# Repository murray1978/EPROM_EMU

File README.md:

# EPROM_EMU
EPROM Emulator for [Sergey's](http://www.malinov.com/Home/sergeys-projects/minimax8085) 8085 board.
Second revison is in progress, 12/5/21, check the readme in version two for errors on the board.

## Programming
The monitor rom can be used to upload the emulator code for the board.
Install the battery backup on to the 8085 borad then you will not need to upload each time you need to use the board.

## Source
As is where is, one carfull lady owner.
Some functions are copied from the monitor code, but it does relie on the monitor rom to setup the 8251 UART before use.
Code is just an outline now with a few ideas in comments.

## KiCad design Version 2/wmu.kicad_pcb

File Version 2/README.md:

# EPROM_EMU
EPROM Emulator for [Sergey's](http://www.malinov.com/Home/sergeys-projects/minimax8085) 8085 board, This is the Second revision.

## Mistakes
1. IC1 (74LS137), Pins 9 and 7, will never get triggered, the correct connections are pins 15 and 14.
   Fix with a solder a jumper bridge between 9 to 15 and 7 to 14. Schmatic is correct

## Substitutions 
1. U1 can be replaced with a 74LS138
2. the RAM, U10 as6c62256, can be replaced with cy62256? need to confirm pinout.

## Programming
The monitor rom can be used to upload the emulator code for the board.
Install the battery backup on to the 8085 borad then you will not need to upload each time you need to use the board.

## Source
As is where is, one carfull lady owner.
Some functions are copied from the monitor code, but it does relie on the monitor rom to setup the 8251 UART before use.
Code is just an outline now with a few ideas in comments.

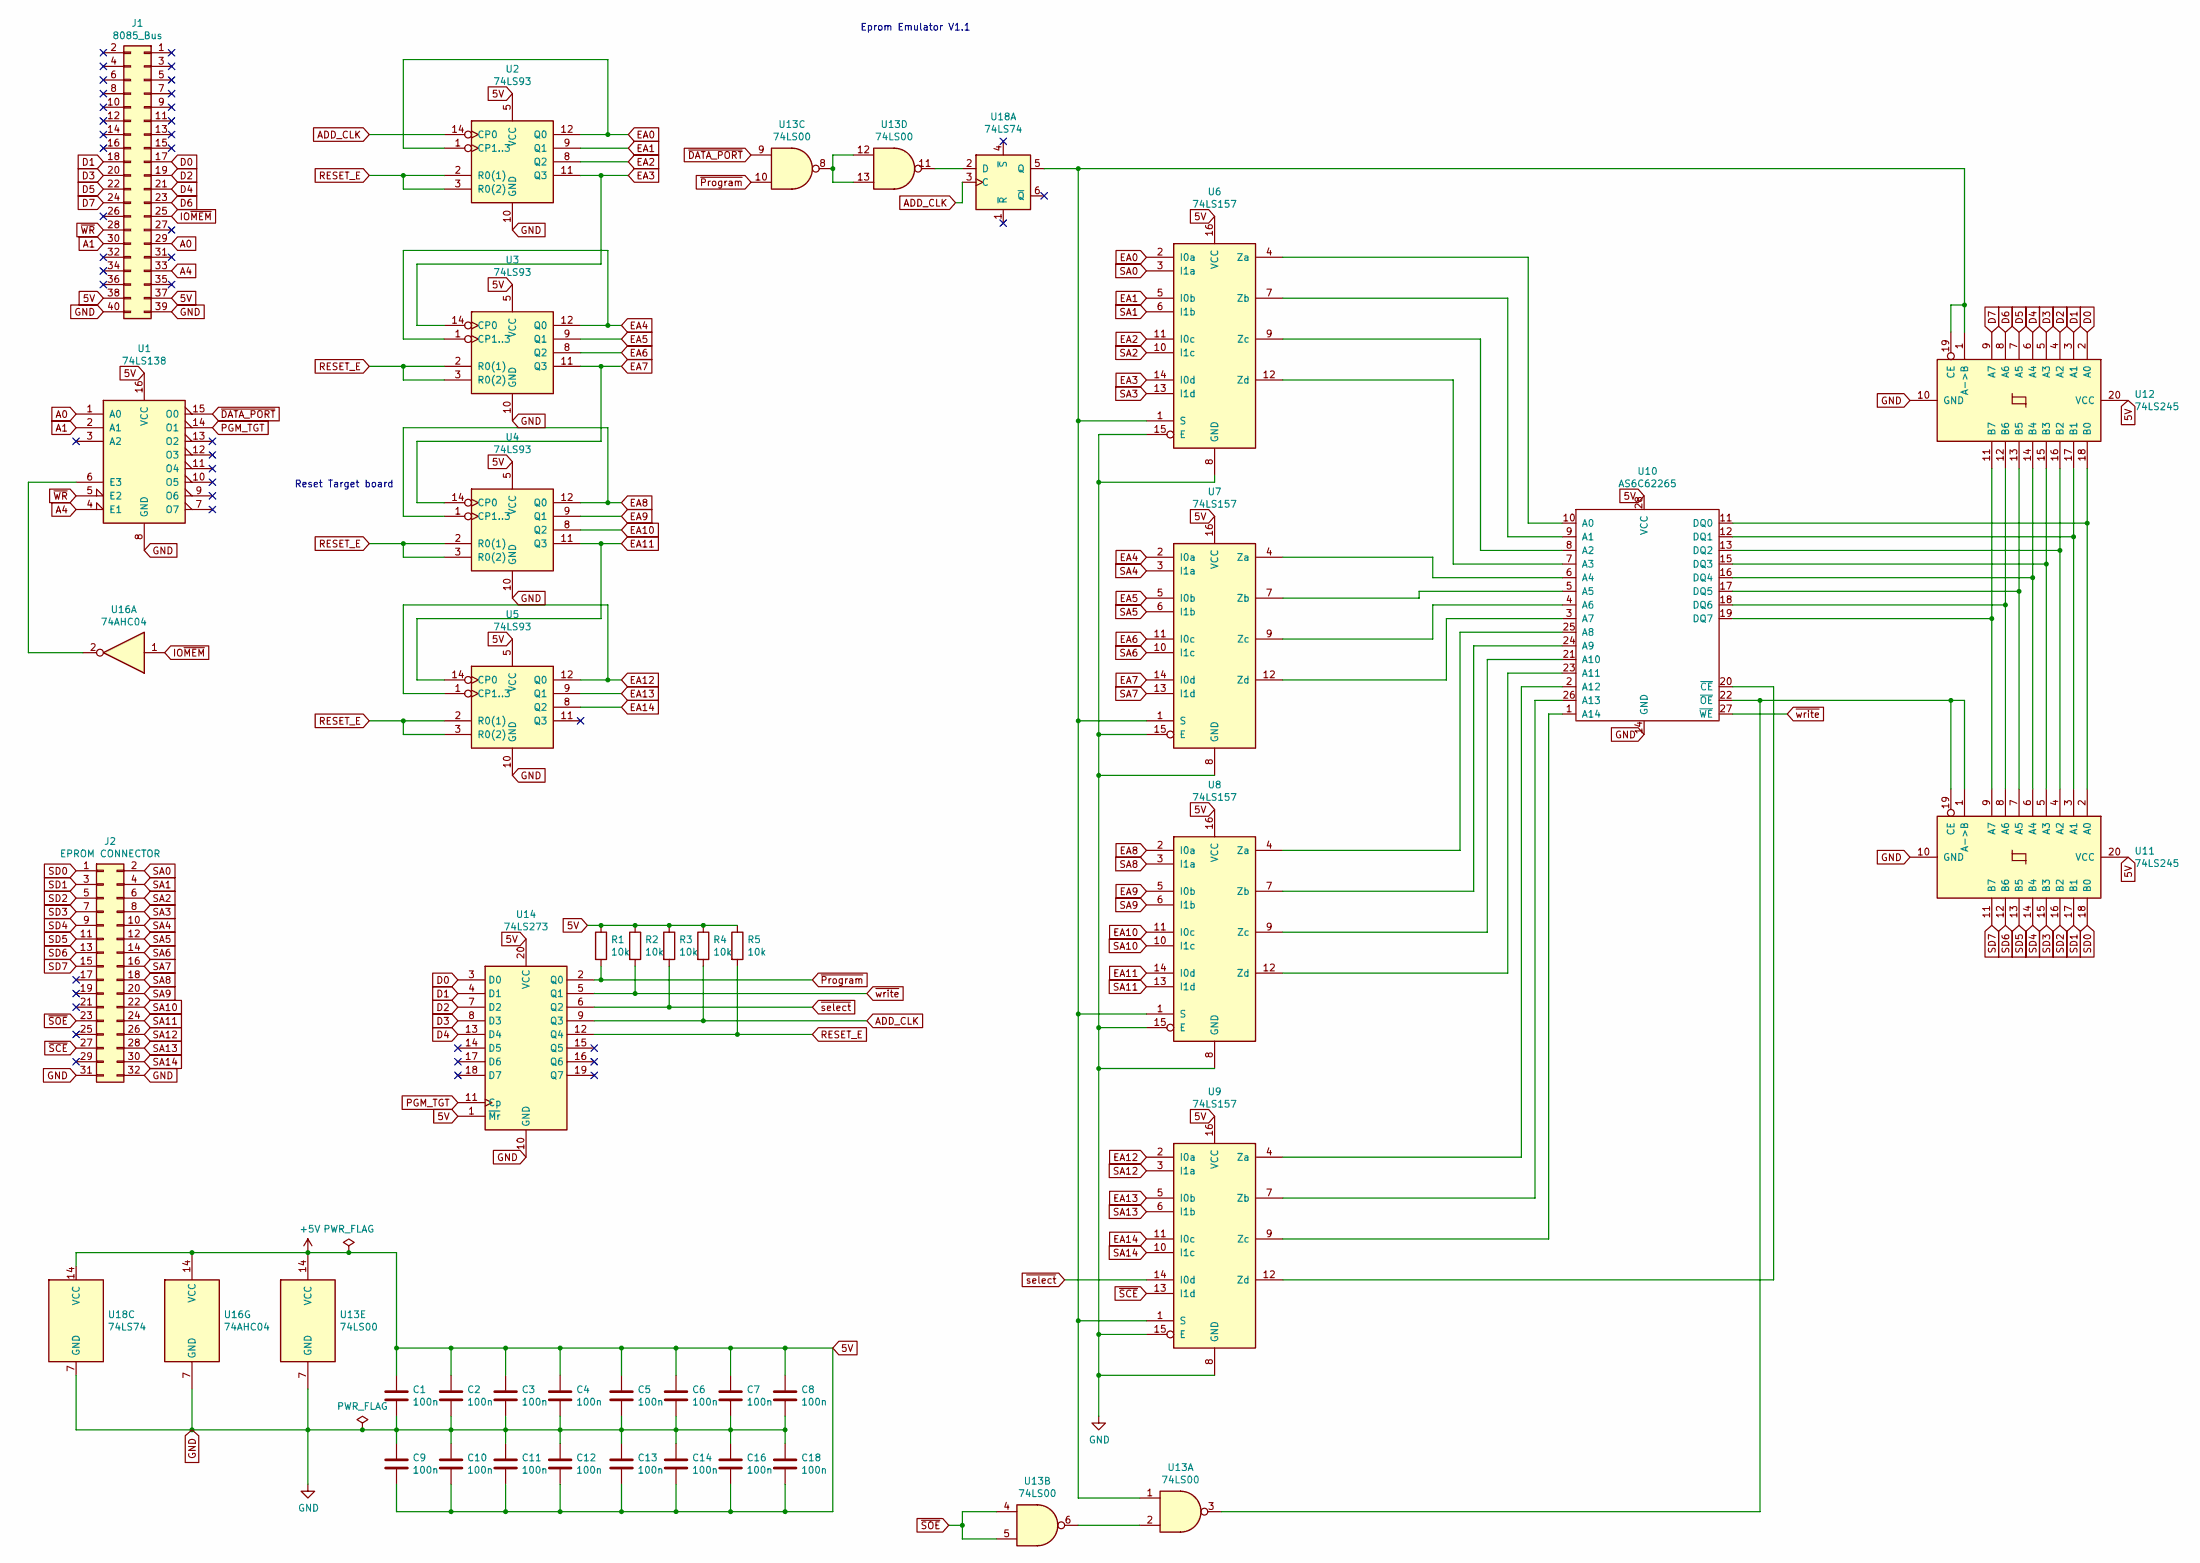
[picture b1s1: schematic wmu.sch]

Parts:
C1, C2, C3, C4, C5, C6, C7, C8, C9, C10, C11, C12, C13, C14, C16, C18: 100n; C_Rect_L7.0mm_W2.5mm_P5.00mm
J1: 8085_Bus; PinSocket_2x20_P2.54mm_Vertical
J2: EPROM CONNECTOR; IDC-Header_2x17_P2.54mm_Vertical
R1, R2, R3, R4, R5: 10k; R_Axial_DIN0207_L6.3mm_D2.5mm_P10.16mm_Horizontal
U1: 74LS138; DIP-16_W7.62mm_LongPads
U2, U3, U4, U5: 74LS93; DIP-14_W7.62mm_Socket
U6, U7, U8, U9: 74LS157; DIP-16_W7.62mm_Socket
U10: AS6C62265; DIP-28_W15.24mm_Socket
U11, U12: 74LS245; DIP-20_W7.62mm_Socket
U13: 74LS00; DIP-14_W7.62mm_Socket
U14: 74LS273; DIP-20_W7.62mm_Socket
U16: 74AHC04; DIP-14_W7.62mm_Socket
U18: 74LS74; DIP-14_W7.62mm_LongPads

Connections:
5V: C1.1, C2.1, C3.1, C4.1, C5.1, C6.1, C7.1, C8.1, C9.2, C10.2, C11.2, C12.2, C13.2, C14.2, C16.2, C18.2, J1.37, J1.38, R1.1, R2.1, R3.1, R4.1, R5.1, U1.16 (VCC), U2.5 (VCC), U3.5 (VCC), U4.5 (VCC), U5.5 (VCC), U6.16 (VCC), U7.16 (VCC), U8.16 (VCC), U9.16 (VCC), U10.28 (VCC), U11.20 (VCC), U12.20 (VCC), U13.14 (VCC), U14.1 (~Mr), U14.20 (VCC), U16.14 (VCC), U18.14 (VCC)
A0: J1.29, U1.1 (A0)
A1: J1.30, U1.2 (A1)
A4: J1.33, U1.4 (E1)
ADD_CLK: R4.2, U2.14 (CP0), U14.9 (Q3), U18.3 (C)
D0: J1.17, U12.2 (A0), U14.3 (D0)
D1: J1.18, U12.3 (A1), U14.4 (D1)
D2: J1.19, U12.4 (A2), U14.7 (D2)
D3: J1.20, U12.5 (A3), U14.8 (D3)
D4: J1.21, U12.6 (A4), U14.13 (D4)
D5: J1.22, U12.7 (A5)
D6: J1.23, U12.8 (A6)
D7: J1.24, U12.9 (A7)
EA0: U2.1 (CP1..3), U2.12 (Q0), U6.2 (I0a)
EA1: U2.9 (Q1), U6.5 (I0b)
EA2: U2.8 (Q2), U6.11 (I0c)
EA3: U2.11 (Q3), U3.14 (CP0), U6.14 (I0d)
EA4: U3.1 (CP1..3), U3.12 (Q0), U7.2 (I0a)
EA5: U3.9 (Q1), U7.5 (I0b)
EA6: U3.8 (Q2), U7.11 (I0c)
EA7: U3.11 (Q3), U4.14 (CP0), U7.14 (I0d)
EA8: U4.1 (CP1..3), U4.12 (Q0), U8.2 (I0a)
EA9: U4.9 (Q1), U8.5 (I0b)
EA10: U4.8 (Q2), U8.11 (I0c)
EA11: U4.11 (Q3), U5.14 (CP0), U8.14 (I0d)
EA12: U5.1 (CP1..3), U5.12 (Q0), U9.2 (I0a)
EA13: U5.9 (Q1), U9.5 (I0b)
EA14: U5.8 (Q2), U9.11 (I0c)
GND: C1.2, C2.2, C3.2, C4.2, C5.2, C6.2, C7.2, C8.2, C9.1, C10.1, C11.1, C12.1, C13.1, C14.1, C16.1, C18.1, J1.39, J1.40, J2.31, J2.32, U1.8 (GND), U2.10 (GND), U3.10 (GND), U4.10 (GND), U5.10 (GND), U6.8 (GND), U6.15 (E), U7.8 (GND), U7.15 (E), U8.8 (GND), U8.15 (E), U9.8 (GND), U9.15 (E), U10.14 (GND), U11.10 (GND), U12.10 (GND), U13.7 (GND), U14.10 (GND), U16.7 (GND), U18.7 (GND)
IO~MEM: J1.25, U16.1
unnamed: U1.6 (E3), U16.2
unnamed: U9.9 (Zc), U10.1 (A14)
unnamed: U9.4 (Za), U10.2 (A12)
unnamed: U7.12 (Zd), U10.3 (A7)
unnamed: U7.9 (Zc), U10.4 (A6)
unnamed: U7.7 (Zb), U10.5 (A5)
unnamed: U7.4 (Za), U10.6 (A4)
unnamed: U6.12 (Zd), U10.7 (A3)
unnamed: U6.9 (Zc), U10.8 (A2)
unnamed: U6.7 (Zb), U10.9 (A1)
unnamed: U6.4 (Za), U10.10 (A0)
unnamed: U10.11 (DQ0), U11.2 (A0), U12.18 (B0)
unnamed: U10.12 (DQ1), U11.3 (A1), U12.17 (B1)
unnamed: U10.13 (DQ2), U11.4 (A2), U12.16 (B2)
unnamed: U10.15 (DQ3), U11.5 (A3), U12.15 (B3)
unnamed: U10.16 (DQ4), U11.6 (A4), U12.14 (B4)
unnamed: U10.17 (DQ5), U11.7 (A5), U12.13 (B5)
unnamed: U10.18 (DQ6), U11.8 (A6), U12.12 (B6)
unnamed: U10.19 (DQ7), U11.9 (A7), U12.11 (B7)
unnamed: U9.12 (Zd), U10.20 (~CE)
unnamed: U8.9 (Zc), U10.21 (A10)
unnamed: U10.22 (~OE), U11.1 (A->B), U11.19 (CE), U13.3
unnamed: U8.12 (Zd), U10.23 (A11)
unnamed: U8.7 (Zb), U10.24 (A9)
unnamed: U8.4 (Za), U10.25 (A8)
unnamed: U9.7 (Zb), U10.26 (A13)
unnamed: U6.1 (S), U7.1 (S), U8.1 (S), U9.1 (S), U12.1 (A->B), U12.19 (CE), U13.1, U18.5 (Q)
unnamed: U13.2, U13.6
unnamed: U13.11, U18.2 (D)
unnamed: U13.8, U13.12, U13.13
PGM_TGT: U1.7 (O7), U1.14 (O1), U14.11 (Cp)
RESET_E: R5.2, U2.2 (R0(1)), U2.3 (R0(2)), U3.2 (R0(1)), U3.3 (R0(2)), U4.2 (R0(1)), U4.3 (R0(2)), U5.2 (R0(1)), U5.3 (R0(2)), U14.12 (Q4)
SA0: J2.2, U6.3 (I1a)
SA1: J2.4, U6.6 (I1b)
SA2: J2.6, U6.10 (I1c)
SA3: J2.8, U6.13 (I1d)
SA4: J2.10, U7.3 (I1a)
SA5: J2.12, U7.6 (I1b)
SA6: J2.14, U7.10 (I1c)
SA7: J2.16, U7.13 (I1d)
SA8: J2.18, U8.3 (I1a)
SA9: J2.20, U8.6 (I1b)
SA10: J2.22, U8.10 (I1c)
SA11: J2.24, U8.13 (I1d)
SA12: J2.26, U9.3 (I1a)
SA13: J2.28, U9.6 (I1b)
SA14: J2.30, U9.10 (I1c)
SD0: J2.1, U11.18 (B0)
SD1: J2.3, U11.17 (B1)
SD2: J2.5, U11.16 (B2)
SD3: J2.7, U11.15 (B3)
SD4: J2.9, U11.14 (B4)
SD5: J2.11, U11.13 (B5)
SD6: J2.13, U11.12 (B6)
SD7: J2.15, U11.11 (B7)
~DATA_PORT: U1.9 (O6), U1.15 (O0), U13.9
~Program: R1.2, U13.10, U14.2 (Q0)
~SCE: J2.27, U9.13 (I1d)
~SOE: J2.23, U13.4, U13.5
~WR: J1.28, U1.5 (E2)
~select: R3.2, U9.14 (I0d), U14.6 (Q2)
~write: R2.2, U10.27 (~WE), U14.5 (Q1)

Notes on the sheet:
Reset Target board
Eprom Emulator V1.1

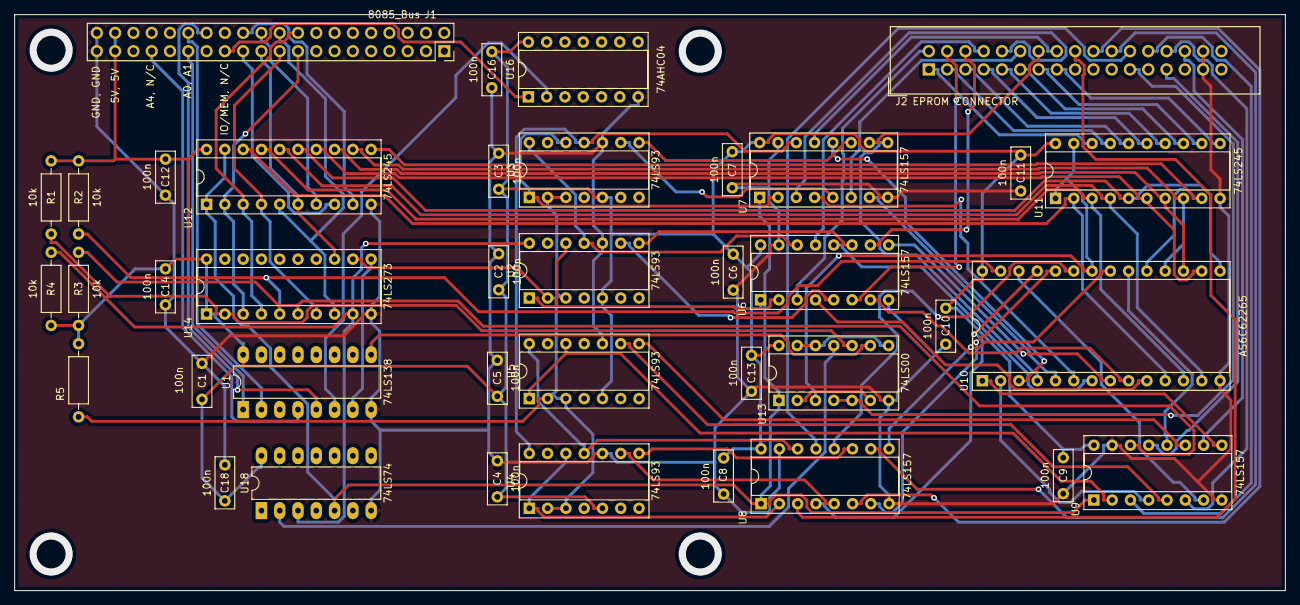
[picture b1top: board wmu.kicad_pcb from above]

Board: 2 copper layers, 176.5 x 80.0 mm, 39 parts (0 on the bottom side), 92 nets.

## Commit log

2020-11-01 Added Source
    Initial commit
2020-11-01 Added Schematic and board
    Initial Commit
2020-11-01 Update README.md
    Initial Readme
2020-11-01 Update README.md
    Formatting and links
2020-11-01 Update README.md
    edit
2020-11-02 Update README.md
    Grammar and spelling fixes.
2020-11-02 Update emu85.asm
    fleshing out main in c
2020-11-05 Update README.md
    update of readme
2020-11-05 Create emu85b.asm
    initial commit
2020-11-05 Update README.md
    update
2021-05-11 Update README.md
    Added note about incorrect pin out for IC1
2021-05-11 Update for second version
2021-05-12 PCB update
    Fixed issue with incorrect pin connections on IC1
